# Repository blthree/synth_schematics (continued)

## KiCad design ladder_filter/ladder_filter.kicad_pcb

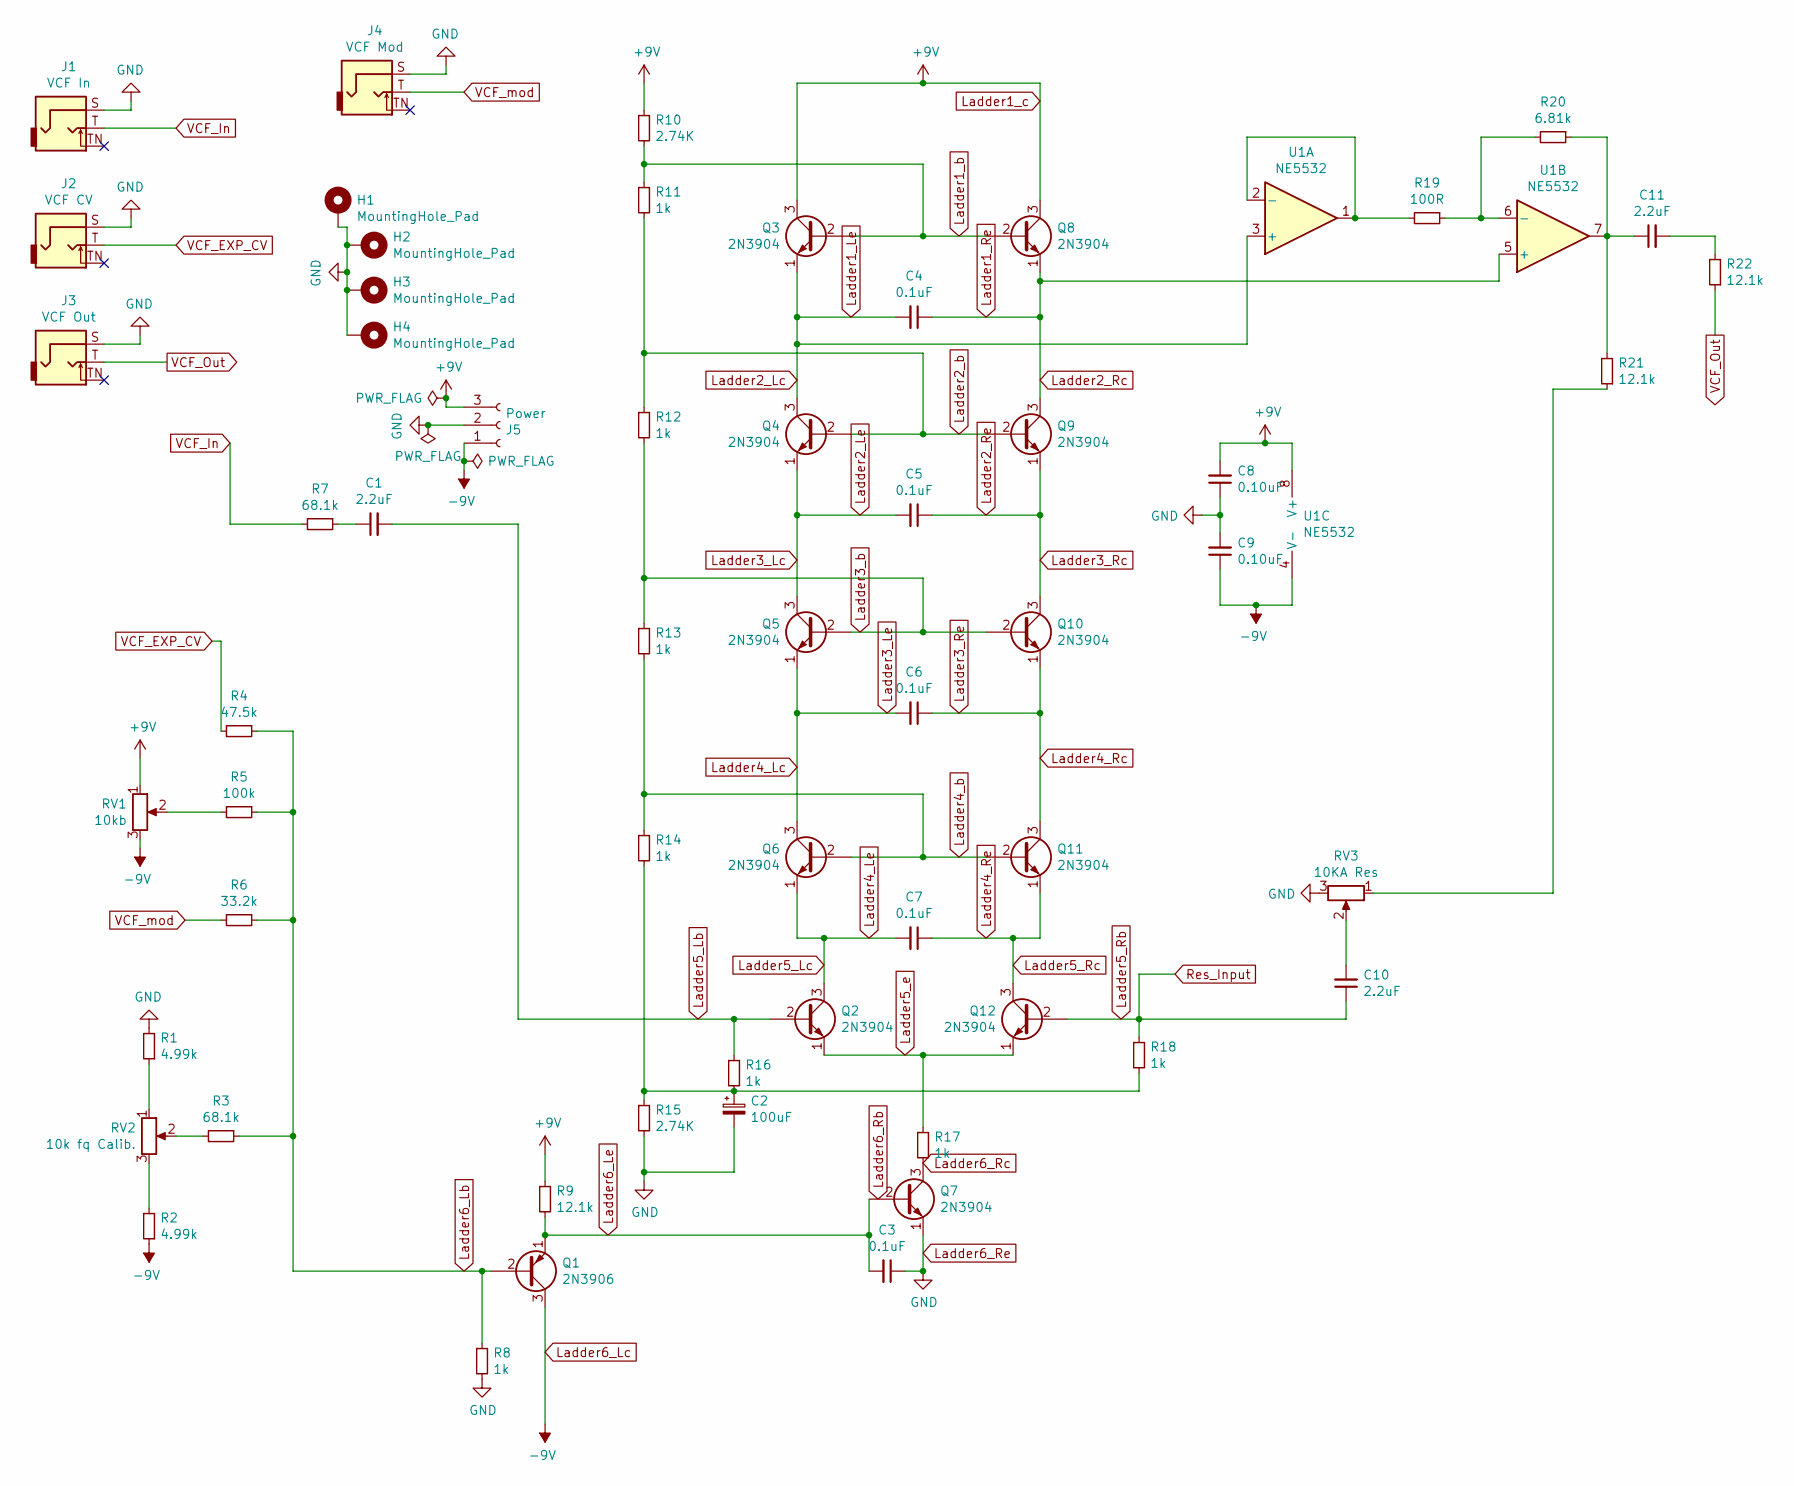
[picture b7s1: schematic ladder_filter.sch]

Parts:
C1, C10, C11: 2.2uF; C_Disc_D4.7mm_W2.5mm_P5.00mm
C2: 100uF; CP_Radial_D5.0mm_P2.50mm
C3, C4, C5, C6, C7: 0.1uF; C_Disc_D4.7mm_W2.5mm_P5.00mm
C8, C9: 0.10uF; C_Disc_D4.7mm_W2.5mm_P5.00mm
H1, H2, H3, H4: MountingHole_Pad; MountingHole_3.2mm_M3_ISO7380_Pad
J1: VCF In; CUI_SJ2-3592B-SMT-TR
J2: VCF CV; CUI_SJ2-3592B-SMT-TR
J3: VCF Out; CUI_SJ2-3592B-SMT-TR
J4: VCF Mod; CUI_SJ2-3592B-SMT-TR
J5: Power; JST_PH_B3B-PH-K_1x03_P2.00mm_Vertical
Q1: 2N3906; TO-92_Inline
Q2, Q3, Q4, Q5, Q6, Q7, Q8, Q9, Q10, Q11, Q12: 2N3904; TO-92_Inline
R1, R2: 4.99k; R_Axial_DIN0207_L6.3mm_D2.5mm_P5.08mm_Vertical
R3, R7: 68.1k; R_Axial_DIN0207_L6.3mm_D2.5mm_P5.08mm_Vertical
R4: 47.5k; R_Axial_DIN0207_L6.3mm_D2.5mm_P5.08mm_Vertical
R5: 100k; R_Axial_DIN0207_L6.3mm_D2.5mm_P5.08mm_Vertical
R6: 33.2k; R_Axial_DIN0207_L6.3mm_D2.5mm_P5.08mm_Vertical
R8, R11, R12, R13, R14, R16, R17, R18: 1k; R_Axial_DIN0207_L6.3mm_D2.5mm_P5.08mm_Vertical
R9, R21, R22: 12.1k; R_Axial_DIN0207_L6.3mm_D2.5mm_P5.08mm_Vertical
R10, R15: 2.74K; R_Axial_DIN0207_L6.3mm_D2.5mm_P5.08mm_Vertical
R19: 100R; R_Axial_DIN0207_L6.3mm_D2.5mm_P5.08mm_Vertical
R20: 6.81k; R_Axial_DIN0207_L6.3mm_D2.5mm_P5.08mm_Vertical
RV1: 10kb; Potentiometer_Bourns_PTV09A-1_Single_Vertical
RV2: 10k fq Calib.; Potentiometer_Bourns_3299W_Vertical
RV3: 10KA Res; Potentiometer_Bourns_PTV09A-1_Single_Vertical
U1: NE5532; DIP-8_W7.62mm_Socket

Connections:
Ladder1_Le: C4.2, Q3.1 (E), Q4.3 (C), U1.3 (+)
Ladder1_Re: C4.1, Q8.1 (E), Q9.3 (C), U1.5 (+)
Ladder1_b: Q3.2 (B), Q8.2 (B), R10.2, R11.1
Ladder1_c: C8.2, J5.3, Q3.3 (C), Q8.3 (C), R9.1, R10.1, RV1.1, U1.8 (V+)
Ladder2_Le: C5.2, Q4.1 (E), Q5.3 (C)
Ladder2_Re: C5.1, Q9.1 (E), Q10.3 (C)
Ladder2_b: Q4.2 (B), Q9.2 (B), R11.2, R12.1
Ladder3_Le: C6.2, Q5.1 (E), Q6.3 (C)
Ladder3_Re: C6.1, Q10.1 (E), Q11.3 (C)
Ladder3_b: Q5.2 (B), Q10.2 (B), R12.2, R13.1
Ladder4_Le: C7.2, Q2.3 (C), Q6.1 (E)
Ladder4_Re: C7.1, Q11.1 (E), Q12.3 (C)
Ladder4_b: Q6.2 (B), Q11.2 (B), R13.2, R14.1
Ladder5_Lb: C1.2, Q2.2 (B), R16.1
Ladder5_Rb: C10.1, Q12.2 (B), R18.1
Ladder5_e: Q2.1 (E), Q12.1 (E), R17.1
Ladder6_Lb: Q1.2 (B), R3.1, R4.1, R5.1, R6.1, R8.1
Ladder6_Lc: C9.1, J5.1, Q1.3 (C), R2.1, RV1.3, U1.4 (V-)
Ladder6_Le: C3.2, Q1.1 (E), Q7.2 (B), R9.2
Ladder6_Rc: Q7.3 (C), R17.2
Ladder6_Re: C2.2, C3.1, C8.1, C9.2, H1.1, H2.1, H3.1, H4.1, J1.S, J2.S, J3.S, J4.S, J5.2, Q7.1 (E), R1.2, R8.2, R15.2, RV3.3
unnamed: C1.1, R7.1
unnamed: C2.1, R14.2, R15.1, R16.2, R18.2
unnamed: C10.2, RV3.2
unnamed: C11.1, R20.1, R21.2, U1.7
unnamed: C11.2, R22.2
unnamed: R1.1, RV2.1
unnamed: R2.2, RV2.3
unnamed: R3.2, RV2.2
unnamed: R5.2, RV1.2
unnamed: R19.1, R20.2, U1.6 (-)
unnamed: R19.2, U1.1, U1.2 (-)
unnamed: R21.1, RV3.1
VCF_EXP_CV: J2.T, R4.2
VCF_In: J1.T, R7.2
VCF_Out: J3.T, R22.1
VCF_mod: J4.T, R6.2

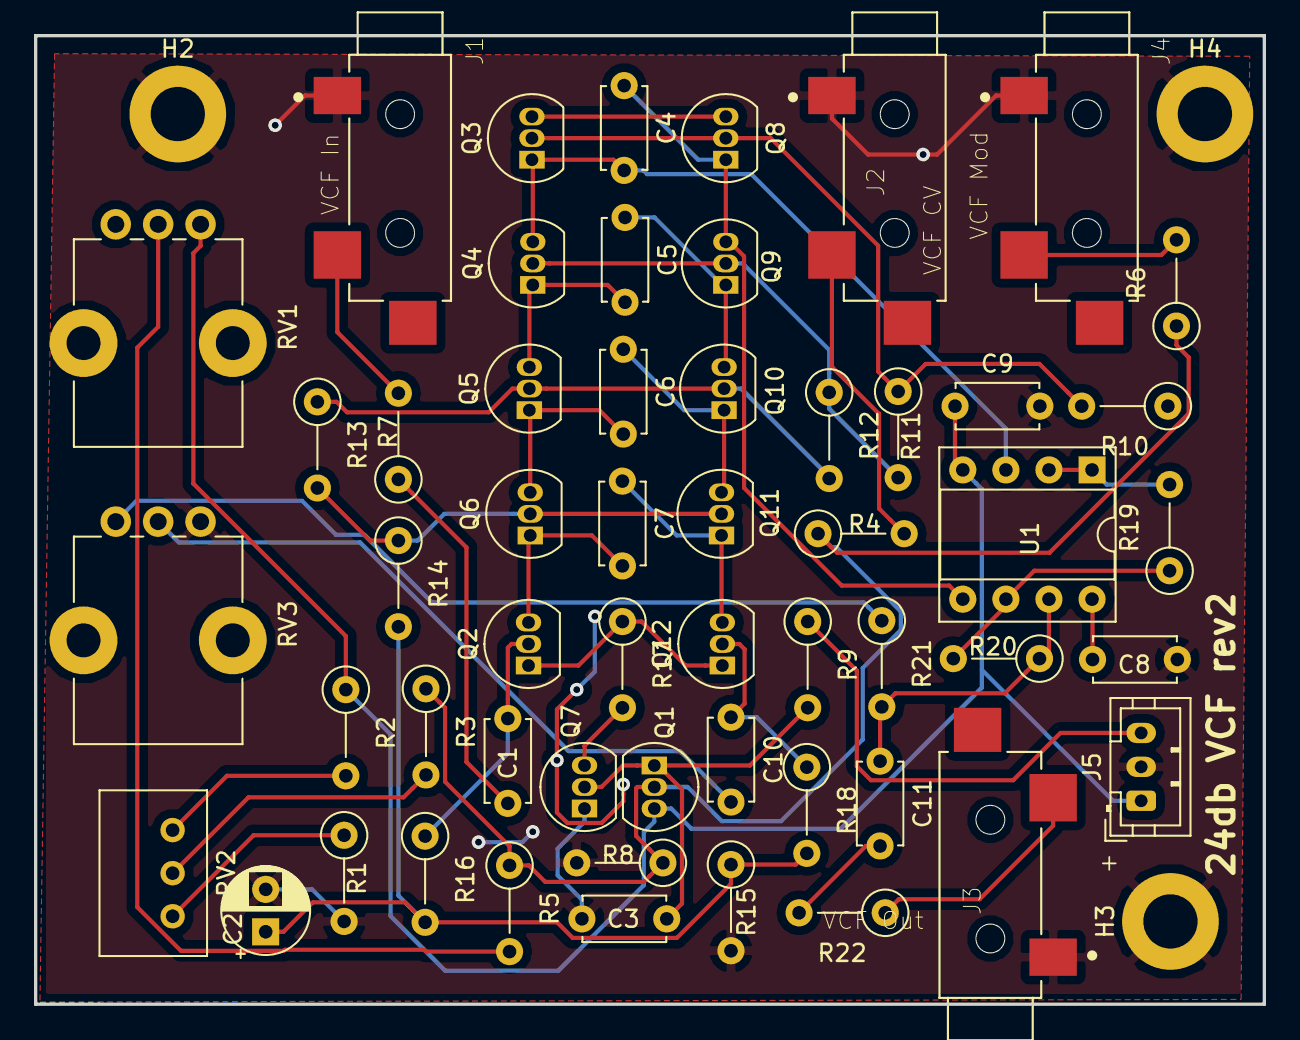
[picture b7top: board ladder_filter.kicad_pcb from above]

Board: 2 copper layers, 72.4 x 57.1 mm, 57 parts (0 on the bottom side), 37 nets.

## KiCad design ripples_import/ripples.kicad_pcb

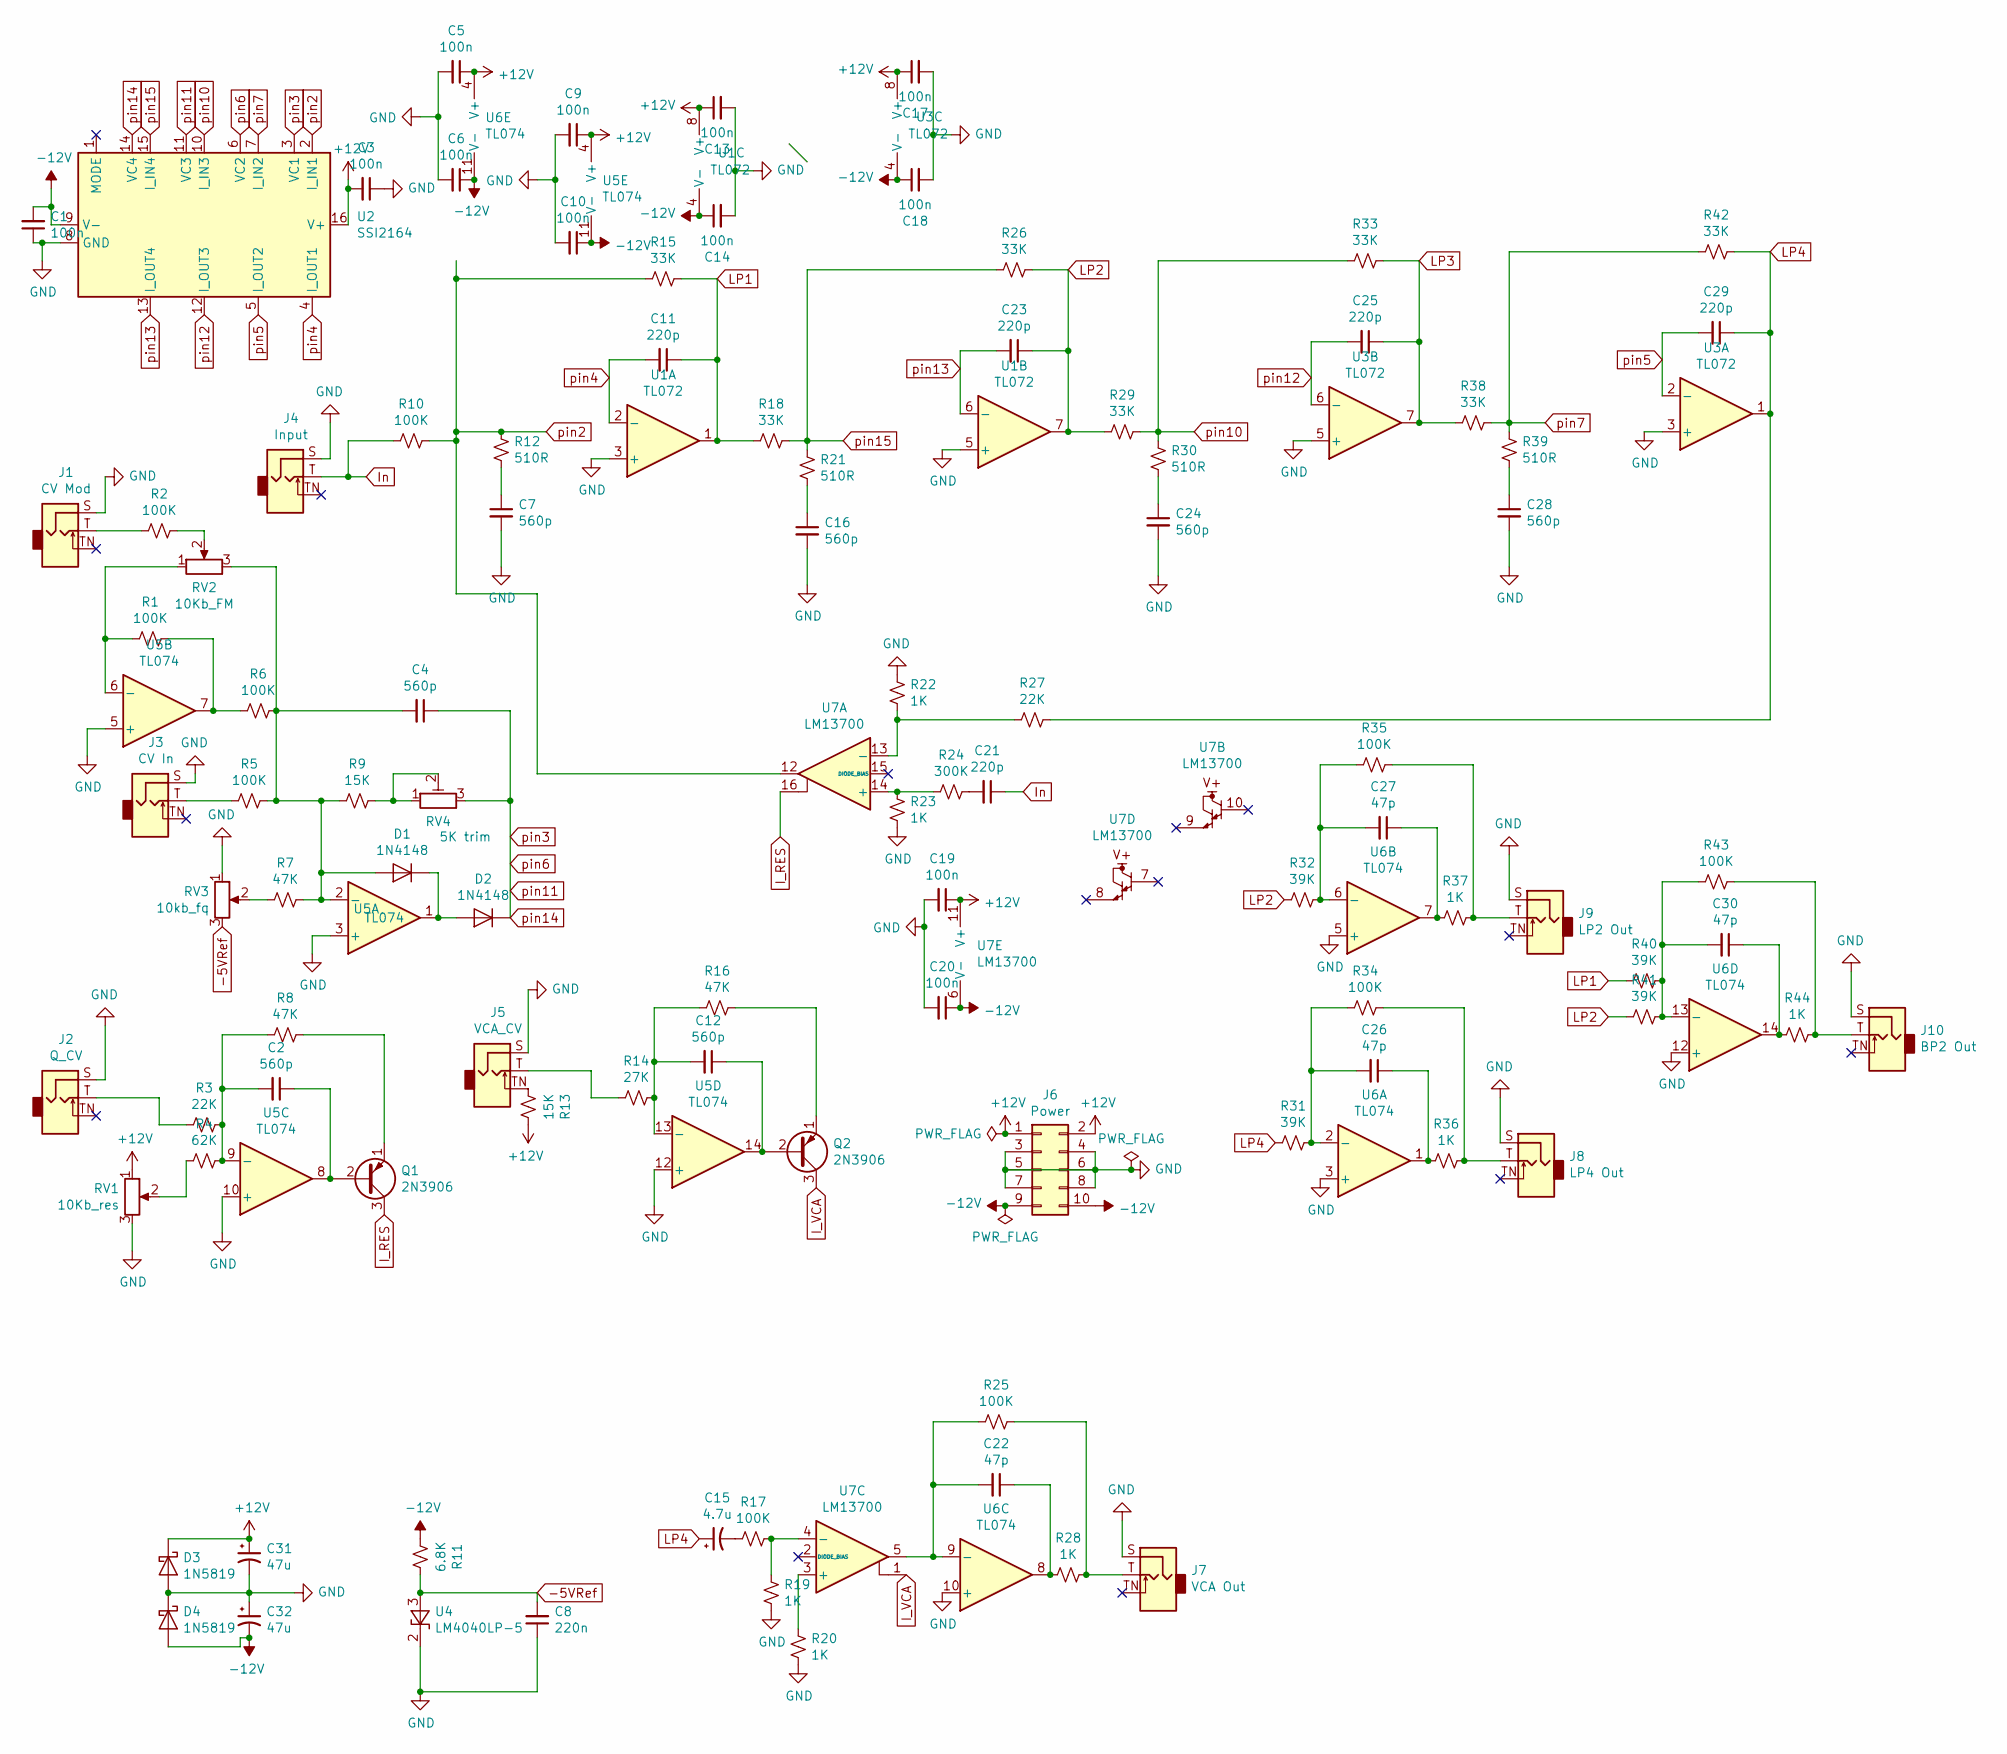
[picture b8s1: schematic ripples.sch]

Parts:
C1, C3, C5, C6, C9, C10, C13, C14, C17, C18, C19, C20: 100n; C_Disc_D5.1mm_W3.2mm_P5.00mm
C2, C4, C7, C12, C16, C24, C28: 560p; C_Disc_D5.1mm_W3.2mm_P5.00mm
C8: 220n; C_Disc_D5.1mm_W3.2mm_P5.00mm
C11, C21, C23, C25, C29: 220p; C_Disc_D5.1mm_W3.2mm_P5.00mm
C15: 4.7u; CP_Radial_D5.0mm_P2.00mm
C22, C26, C27, C30: 47p; C_Disc_D5.1mm_W3.2mm_P5.00mm
C31, C32: 47u; CP_Radial_D5.0mm_P2.00mm
D1, D2: 1N4148; D_DO-35_SOD27_P7.62mm_Horizontal
D3, D4: 1N5819; D_DO-41_SOD81_P10.16mm_Horizontal
J1: CV Mod; Jack_3.5mm_QingPu_WQP-PJ398SM_Vertical_CircularHoles
J2: Q_CV; Jack_3.5mm_QingPu_WQP-PJ398SM_Vertical_CircularHoles
J3: CV In; Jack_3.5mm_QingPu_WQP-PJ398SM_Vertical_CircularHoles
J4: Input; Jack_3.5mm_QingPu_WQP-PJ398SM_Vertical_CircularHoles
J5: VCA_CV; Jack_3.5mm_QingPu_WQP-PJ398SM_Vertical_CircularHoles
J6: Power; PinHeader_2x05_P2.54mm_Vertical
J7: VCA Out; Jack_3.5mm_QingPu_WQP-PJ398SM_Vertical_CircularHoles
J8: LP4 Out; Jack_3.5mm_QingPu_WQP-PJ398SM_Vertical_CircularHoles
J9: LP2 Out; Jack_3.5mm_QingPu_WQP-PJ398SM_Vertical_CircularHoles
J10: BP2 Out; Jack_3.5mm_QingPu_WQP-PJ398SM_Vertical_CircularHoles
Q1, Q2: 2N3906; TO-92_Inline
R1, R2, R5, R6, R10, R17, R25, R34, R35, R43: 100K; R_Axial_DIN0207_L6.3mm_D2.5mm_P5.08mm_Vertical
R3, R27: 22K; R_Axial_DIN0207_L6.3mm_D2.5mm_P5.08mm_Vertical
R4: 62K; R_Axial_DIN0207_L6.3mm_D2.5mm_P5.08mm_Vertical
R7, R8, R16: 47K; R_Axial_DIN0207_L6.3mm_D2.5mm_P5.08mm_Vertical
R9, R13: 15K; R_Axial_DIN0207_L6.3mm_D2.5mm_P5.08mm_Vertical
R11: 6.8K; R_Axial_DIN0207_L6.3mm_D2.5mm_P5.08mm_Vertical
R12, R21, R30, R39: 510R; R_Axial_DIN0207_L6.3mm_D2.5mm_P5.08mm_Vertical
R14: 27K; R_Axial_DIN0207_L6.3mm_D2.5mm_P5.08mm_Vertical
R15, R18, R26, R29, R33, R38, R42: 33K; R_Axial_DIN0207_L6.3mm_D2.5mm_P5.08mm_Vertical
R19, R20, R22, R23, R28, R36, R37, R44: 1K; R_Axial_DIN0207_L6.3mm_D2.5mm_P5.08mm_Vertical
R24: 300K; R_Axial_DIN0207_L6.3mm_D2.5mm_P5.08mm_Vertical
R31, R32, R40, R41: 39K; R_Axial_DIN0207_L6.3mm_D2.5mm_P5.08mm_Vertical
RV1: 10Kb_res; Potentiometer_Bourns_PTV09A-1_Single_Vertical
RV2: 10Kb_FM; Potentiometer_Bourns_PTV09A-1_Single_Vertical
RV3: 10kb_fq; Potentiometer_Bourns_PTV09A-1_Single_Vertical
RV4: 5K trim; Potentiometer_Bourns_3296X_Horizontal
U1, U3: TL072; DIP-8_W7.62mm_Socket
U2: SSI2164; DIP-16_W7.62mm_Socket
U4: LM4040LP-5; TO-92_Inline
U5, U6: TL074; DIP-14_W7.62mm_Socket
U7: LM13700; DIP-16_W7.62mm_Socket

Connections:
+12V: C3.2, C5.1, C9.1, C13.1, C17.1, C19.1, C31.1, D3.1 (K), J6.1, J6.2, R13.1, RV1.1, U1.8 (V+), U2.16 (V+), U3.8 (V+), U5.4 (V+), U6.4 (V+), U7.11 (V+)
-5VRef: C8.2, R11.1, RV3.3, U4.3 (A)
-12V: C1.2, C6.1, C10.1, C14.1, C18.1, C20.1, C32.2, D4.2 (A), J6.9, J6.10, R11.2, U1.4 (V-), U2.9 (V-), U3.4 (V-), U5.11 (V-), U6.11 (V-), U7.6 (V-)
GND: C1.1, C3.1, C5.2, C6.2, C7.2, C8.1, C9.2, C10.2, C13.2, C14.2, C16.2, C17.2, C18.2, C19.2, C20.2, C24.2, C28.2, C31.2, C32.1, D3.2 (A), D4.1 (K), J1.S, J2.S, J3.S, J4.S, J5.S, J6.3, J6.4, J6.5, J6.6, J6.7, J6.8, J7.S, J8.S, J9.S, J10.S, R19.1, R20.1, R22.2, R23.1, RV1.3, RV3.1, U1.3 (+), U1.5 (+), U2.8 (GND), U3.3 (+), U3.5 (+), U4.2 (K), U5.3 (+), U5.5 (+), U5.10 (+), U5.12 (+), U6.3 (+), U6.5 (+), U6.10 (+), U6.12 (+)
I_RES: Q1.3 (C), U7.16
I_VCA: Q2.3 (C), U7.1
In: C21.1, J4.T, R10.2
LP1: C11.1, R15.2, R18.1, R40.2, U1.1
LP2: C23.1, R26.2, R29.1, R32.2, R41.2, U1.7
LP3: C25.1, R33.2, R38.1, U3.7
LP4: C15.1, C29.1, R27.2, R31.2, R42.2, U3.1
unnamed: C2.1, Q1.2 (B), U5.8
unnamed: C2.2, R3.1, R4.1, R8.2, U5.9 (-)
unnamed: C4.2, D1.2 (A), R5.1, R6.1, R7.1, R9.2, RV2.3, U5.2 (-)
unnamed: C7.1, R12.1
unnamed: C12.1, Q2.2 (B), U5.14
unnamed: C12.2, R14.1, R16.2, U5.13 (-)
unnamed: C15.2, R17.2
unnamed: C16.1, R21.1
unnamed: C21.2, R24.2
unnamed: C22.1, R28.1, U6.8
unnamed: C22.2, R25.2, U6.9 (-), U7.5
unnamed: C24.1, R30.1
unnamed: C26.1, R36.1, U6.1
unnamed: C26.2, R31.1, R34.2, U6.2 (-)
unnamed: C27.1, R37.1, U6.7
unnamed: C27.2, R32.1, R35.2, U6.6 (-)
unnamed: C28.1, R39.1
unnamed: C30.1, R44.1, U6.14
unnamed: C30.2, R40.1, R41.1, R43.2, U6.13 (-)
unnamed: D1.1 (K), D2.2 (A), U5.1
unnamed: J1.T, R2.2
unnamed: J2.T, R3.2
unnamed: J3.T, R5.2
unnamed: J5.T, R14.2
unnamed: J5.TN, R13.2
unnamed: J7.T, R25.1, R28.2
unnamed: J8.T, R34.1, R36.2
unnamed: J9.T, R35.1, R37.2
unnamed: J10.T, R43.1, R44.2
unnamed: Q1.1 (E), R8.1
unnamed: Q2.1 (E), R16.1
unnamed: R1.1, R6.2, U5.7
unnamed: R1.2, RV2.1, U5.6 (-)
unnamed: R2.1, RV2.2
unnamed: R4.2, RV1.2
unnamed: R7.2, RV3.2
unnamed: R9.1, RV4.1, RV4.2
unnamed: R17.1, R19.2, U7.4 (-)
unnamed: R20.2, U7.3 (+)
unnamed: R22.1, R27.1, U7.13 (-)
unnamed: R23.2, R24.1, U7.14 (+)
pin2: R10.1, R12.2, R15.1, U2.2 (I_IN1), U7.12
pin4: C11.2, U1.2 (-), U2.4 (I_OUT1)
pin5: C29.2, U2.5 (I_OUT2), U3.2 (-)
pin7: R38.2, R39.2, R42.1, U2.7 (I_IN2)
pin10: R29.2, R30.2, R33.1, U2.10 (I_IN3)
pin11: C4.1, D2.1 (K), RV4.3, U2.3 (VC1), U2.6 (VC2), U2.11 (VC3), U2.14 (VC4)
pin12: C25.2, U2.12 (I_OUT3), U3.6 (-)
pin13: C23.2, U1.6 (-), U2.13 (I_OUT4)
pin15: R18.2, R21.2, R26.1, U2.15 (I_IN4)

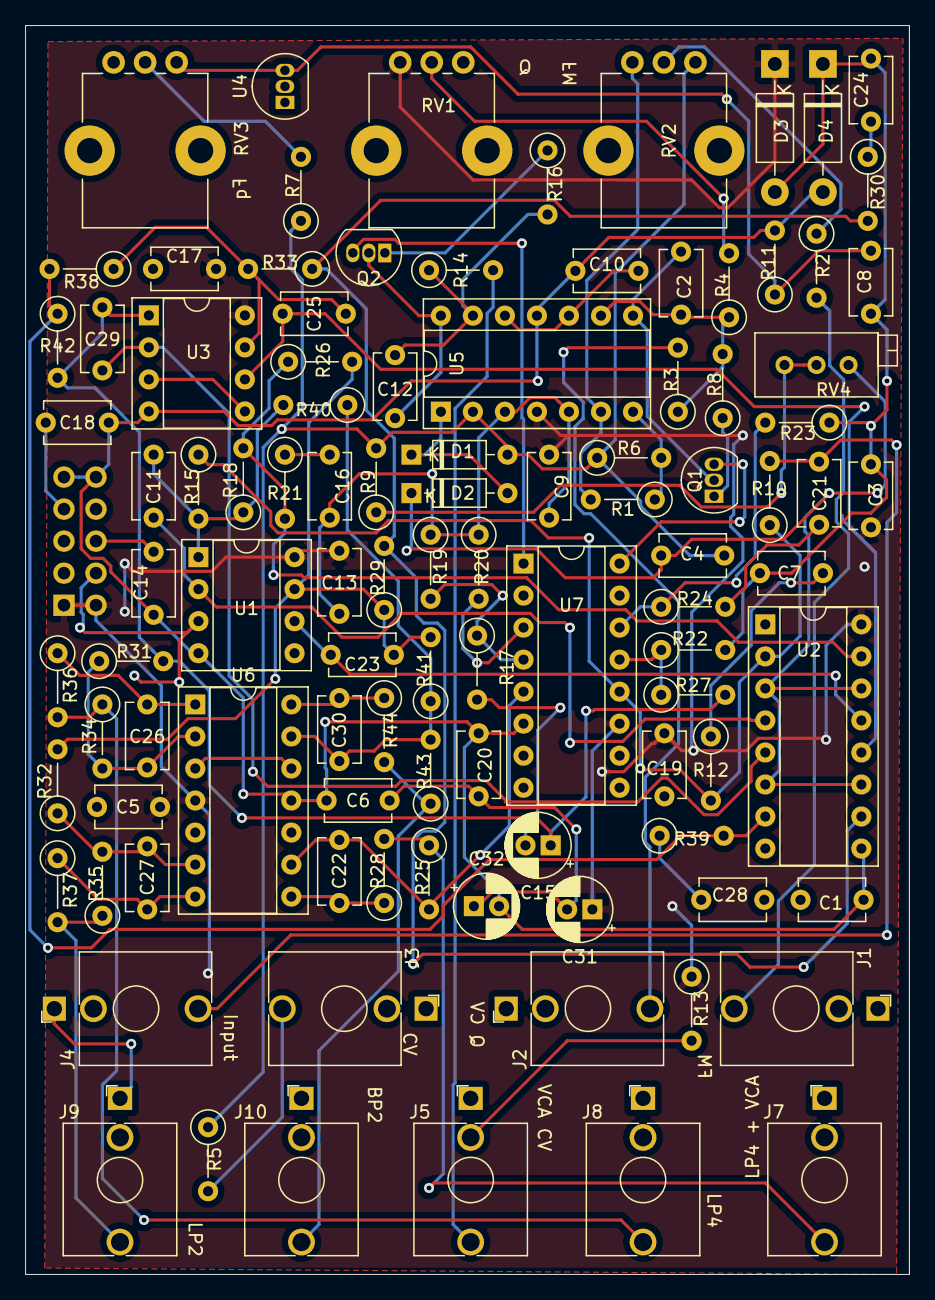
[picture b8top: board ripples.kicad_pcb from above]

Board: 2 copper layers, 70.1 x 99.1 mm, 103 parts (1 on the bottom side), 61 nets.

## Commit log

2019-06-27 Backlink to CADLAB.io has been added.
